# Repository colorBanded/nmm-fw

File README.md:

# Not My Macro!
A custom macropad designed as a submission for the **2025 Summer of Code** by GitHub.
Based on the [AOI3 PCB tutorial](https://wiki.ai03.com/) with modifications for practical use.

# IMPORTANT
###### After reviewing the submission guidelines I removed a key to comply with the less than 16 inputs.

## Features
* 15 Programmable Keys
* XIAO RP2040 Microcontroller
* Highly Customizable
* Easy Dissassembly

# Cad Model:
###### For some reason Fusion 360 was bugging out while rendering the colors so enjoy the light mode experience

I engineered the top so that it slots in without any screws, making it easily detachable, I made sure that theres a tight tolerance so that it doesn't fall apart when you pick it up.
There are 15 Keys that you can customize in the firmware.

Fusion 360 Renderer thingy, everything stacks (Couldn't find a proper stl for the switches and springs but those go under the top case)

Default view, only two outer pieces, cool!

# PCB

I used KiCad to create the PCB assembly, used their built-in image converter to add the graphic.

# Firmware & Layout

I utilized the QMK firmware to handle key inputs. Use the USB C port to flash the .bin file to change layout (Better editor coming soon™)
A key changing tool like AutoHotKey is recommended, if you would like to change the keybinds yourself you can use [QMK Configurator](https://config.qmk.fm/#/atset/at16/LAYOUT_ortho_4x4)

###### This is the current key layout (DDR Reference), F13 through F24 are configured so that it doesn't interfere with any users' existing setup.

# BOM
| Item                                      | Quantity / Notes                                  |
|-------------------------------------------|----------------------------------------------------|
| Cherry MX Switches                        | 15                                                 |
| DSA Keycaps                               | 15                                                 |
| XIAO RP2040-DIP                           | 1                                                  |
| SK6812MINI LEDs                           | 2                                                  |
| Soldering Iron                            | 1                                                  |
| Case                                      | 1 (3D Printed or Laser Cut – laser cut preferred) |
| Generic Diodes (SMD D_SOD-123)            | 15                                                 |
| Assembly Time                             | Approx. 2 hours 30 minutes                         |

## Software Tools

* **PCB Design & Layout**: [KiCAD](https://www.kicad.org/)
* **3D Modeling**: [Fusion 360](https://www.autodesk.com/products/fusion-360/overview)

## References

* [AI03 Wiki](https://wiki.ai03.com/) – General information and guides on PCB design
* [Hack Club PCB Starter Guide](https://hackpad.hackclub.com/) – A beginner-friendly tutorial which this project is based on

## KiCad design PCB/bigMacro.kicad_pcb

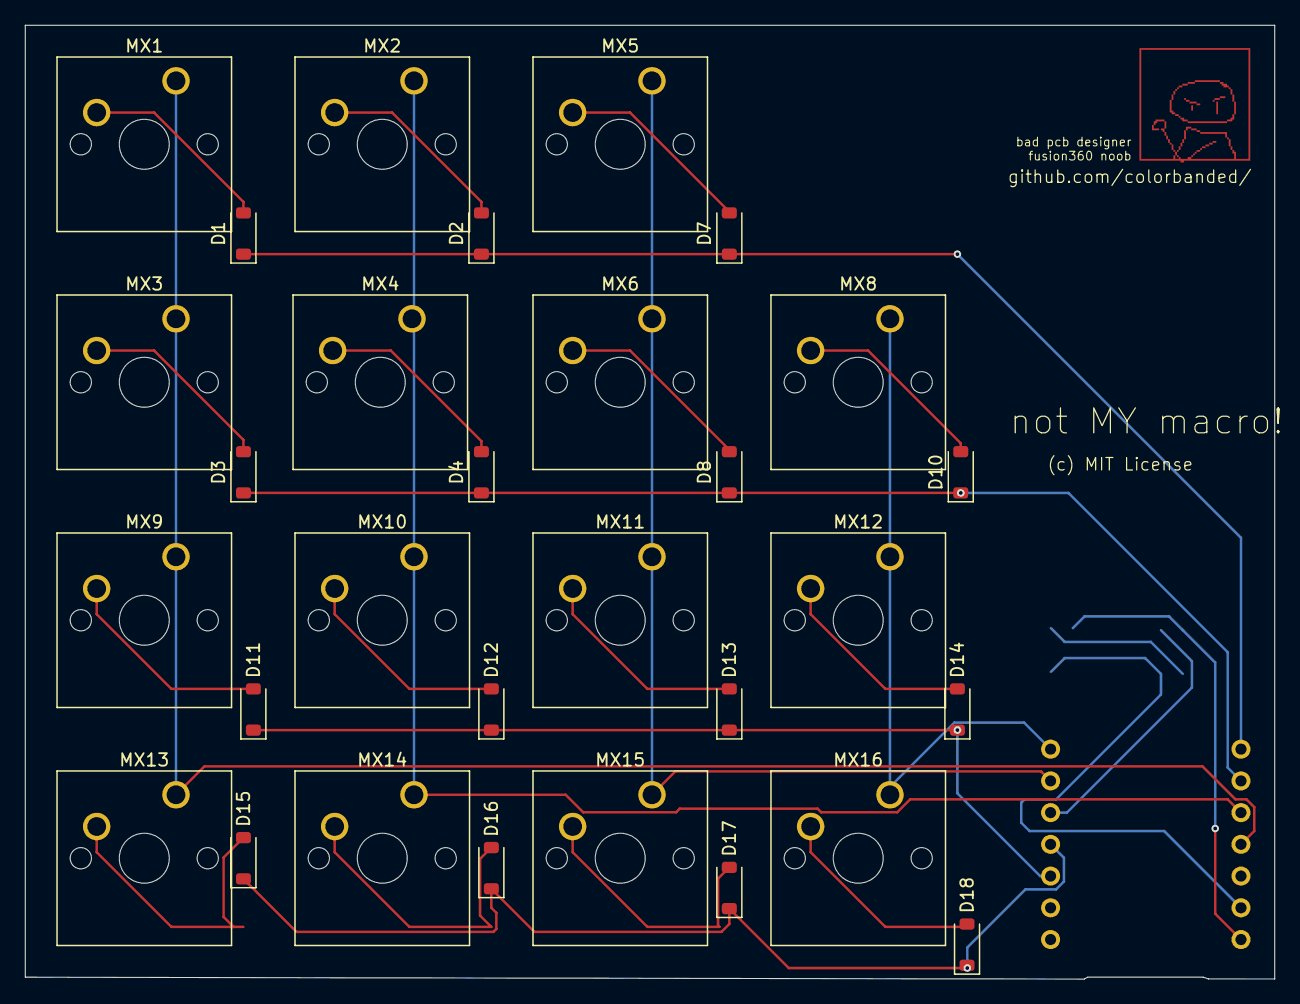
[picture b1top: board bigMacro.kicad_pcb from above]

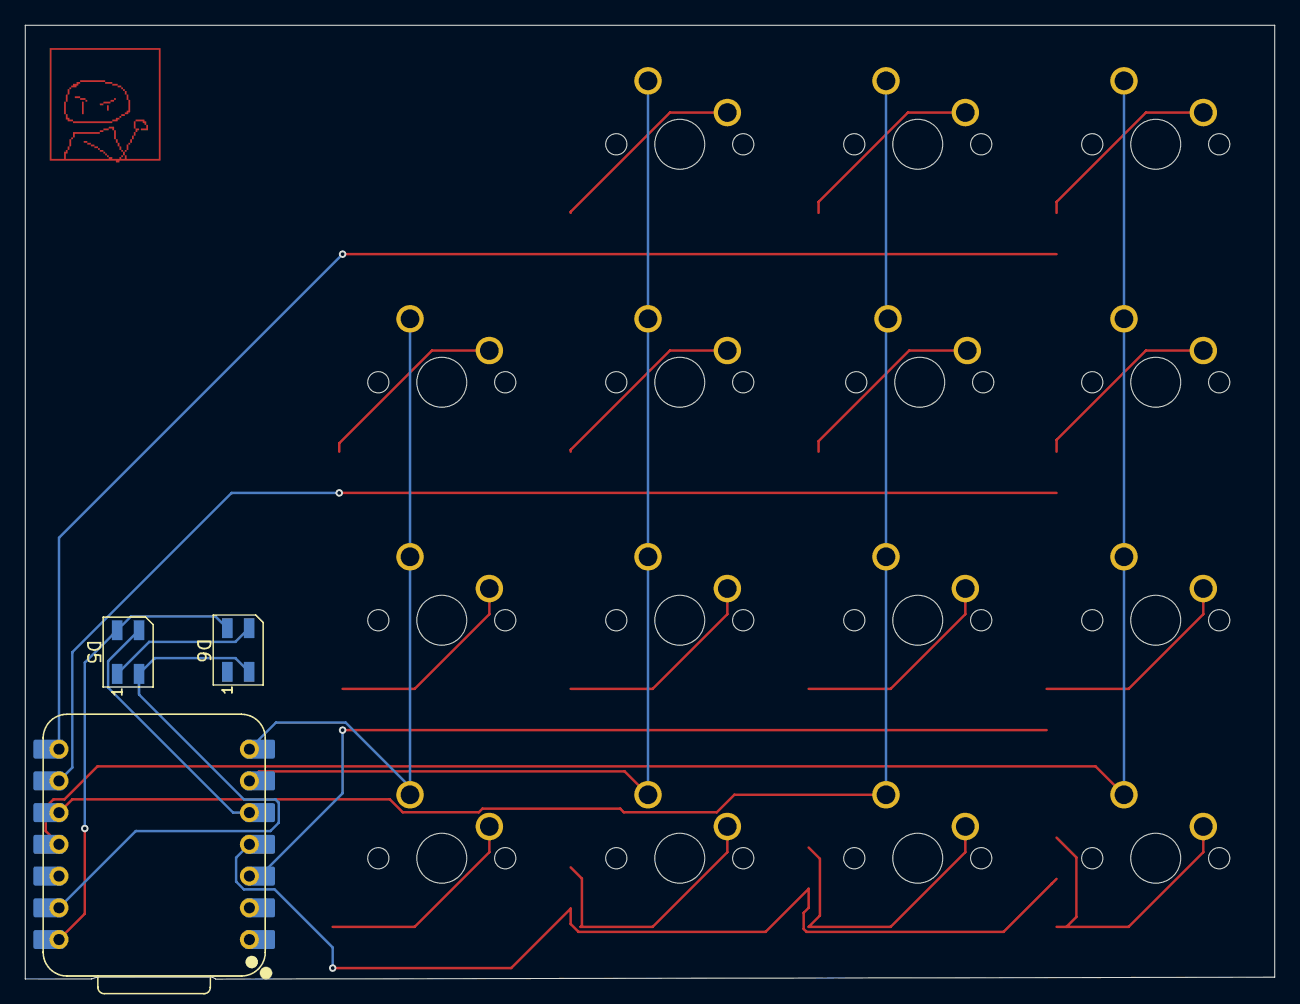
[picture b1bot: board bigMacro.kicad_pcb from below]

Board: 2 copper layers, 100.0 x 76.3 mm, 33 parts (3 on the bottom side), 27 nets.

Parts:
D1, D2, D3, D4, D7, D8, D10, D11, D12, D13, D14, D15, D16, D17, D18: D_Small; D_SOD-123
D5, D6: SK6812MINI; LED_SK6812MINI_PLCC4_3.5x3.5mm_P1.75mm
MX1, MX2, MX3, MX4, MX5, MX6, MX8, MX9, MX10, MX11, MX12, MX13, MX14, MX15, MX16: MX-NoLED; SW_Cherry_MX_1.00u_PCB
U2: XIAO-RP2040-DIP

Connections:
+5V: D5.4 (VDD), D6.4 (VDD), U2.14 (VBUS)
/COL0: MX1.1 (COL), MX3.1 (COL), MX9.1 (COL), MX13.1 (COL), U2.11 (GPIO3/MOSI)
/COL1: MX2.1 (COL), MX4.1 (COL), MX10.1 (COL), MX14.1 (COL), U2.10 (GPIO4/MISO)
/COL2: MX5.1 (COL), MX6.1 (COL), MX11.1 (COL), MX15.1 (COL), U2.6 (GPIO7/SCL)
/COL3: MX8.1 (COL), MX12.1 (COL), MX16.1 (COL), U2.7 (GPIO0/TX)
/ROW0: D1.1 (K), D2.1 (K), D7.1 (K), U2.8 (GPIO1/RX)
/ROW1: D3.1 (K), D4.1 (K), D8.1 (K), D10.1 (K), U2.9 (GPIO2/SCK)
/ROW2: D11.1 (K), D12.1 (K), D13.1 (K), D14.1 (K), U2.3 (GPIO28/ADC2/A2)
/ROW3: D15.1 (K), D16.1 (K), D17.1 (K), D18.1 (K), U2.4 (GPIO29/ADC3/A3)
GND: D5.2 (VSS), D6.2 (VSS), U2.13 (GND)
unnamed: D1.2 (A), MX1.2 (ROW)
unnamed: D2.2 (A), MX2.2 (ROW)
unnamed: D3.2 (A), MX3.2 (ROW)
unnamed: D4.2 (A), MX4.2 (ROW)
unnamed: D5.3 (DIN), U2.5 (GPIO6/SDA)
unnamed: D5.1 (DOUT), D6.3 (DIN)
unnamed: D7.2 (A), MX5.2 (ROW)
unnamed: D8.2 (A), MX6.2 (ROW)
unnamed: D10.2 (A), MX8.2 (ROW)
unnamed: D11.2 (A), MX9.2 (ROW)
unnamed: D12.2 (A), MX10.2 (ROW)
unnamed: D13.2 (A), MX11.2 (ROW)
unnamed: D14.2 (A), MX12.2 (ROW)
unnamed: D15.2 (A), MX13.2 (ROW)
unnamed: D16.2 (A), MX14.2 (ROW)
unnamed: D17.2 (A), MX15.2 (ROW)
unnamed: D18.2 (A), MX16.2 (ROW)

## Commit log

2025-06-27 Add basic PCB junk
2025-06-27 Added Gitignore
2025-06-27 Initial PCB Design (Unfinished)
    Started work on the keyboard layout
2025-06-27 Finished Base PCB Layout
2025-06-27 Finish PCB Design
2025-06-27 Push Changes
2025-06-27 Journal.md
2025-06-28 Upd JMD
2025-06-28 Added 3D Enclosure Model
    Compatible with most 3D printers (Hopefully)
2025-06-28 Added bill of materials as CSV Document
2025-06-28 Folder Restructuring
2025-06-28 auto-save: bigMacro
2025-06-28 Rename README.md to README-V1.md
2025-06-28 New file: Firmware/a
2025-06-28 Uploaded firmware file
2025-06-28 Organize and clean up repository
2025-06-28 RE: Organization, Fixed readme location
2025-06-28 deleted file: .DS_Store
2025-06-28 Update PCB Layout based on requirements
2025-06-28 Added Individual CAD Files
2025-06-28 Updated Firmware
2025-06-28 Added Production Files
2025-06-28 PCB Design update
2025-06-28 Redid PCB
2025-06-28 Removed one key from everything
2025-06-28 Update Production
2025-06-28 Update Production files

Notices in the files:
PCB/bigMacro.kicad_pcb:
(c) MIT License
